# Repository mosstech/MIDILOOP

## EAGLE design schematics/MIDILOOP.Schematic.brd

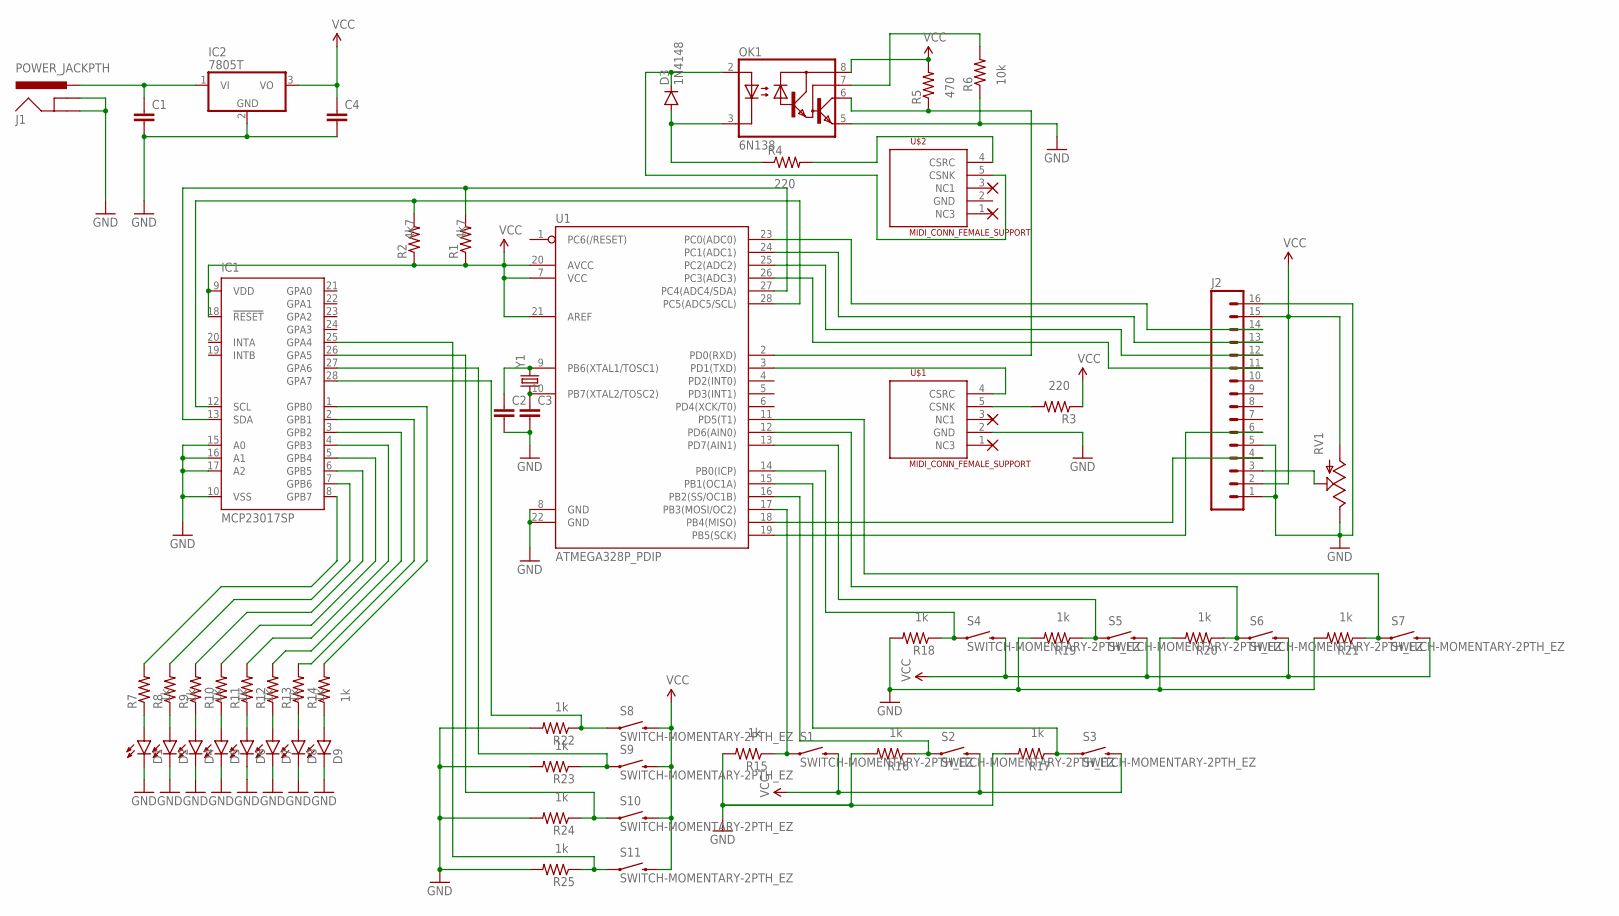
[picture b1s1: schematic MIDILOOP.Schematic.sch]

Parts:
C1, C4: CAPPTH1; CAP-PTH-5MM
C2, C3: CAPPTH; CAP-PTH-SMALL
D1, D2, D4, D5, D6, D7, D8, D9: LED3MM
D3: 1N4148; DIODE-1N4148
IC1: MCP23017SP; DIL28-3
IC2: 7805T; TO220H
J1: POWER_JACKPTH; POWER_JACK_PTH
J2: M16LONGPADS; 1X16_LONGPADS
OK1: 6N138; DIL08
R1, R2, R3, R4, R5, R6, R7, R8, R9, R10, R11, R12, R13, R14, R15, R16, R17, R18, R19, R20, R21, R22, R23, R24, R25: RESISTOREZ; AXIAL-0.3EZ
RV1: POTTRIM; TRIM_POT
S1, S2, S3, S4, S5, S6, S7, S8, S9, S10, S11: SWITCH-MOMENTARY-2PTH_EZ; TACTILE-PTH-EZ
U1: ATMEGA328P_PDIP; DIL28-3
U$1, U$2: MIDI_CONN_FEMALE_SUPPORT; DIN_5_FEMALE_SUPPORT
Y1: CRYSTALHC49US; HC49US

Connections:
GND: C1.2, C2.2, C3.2, C4.2, D1.K (C), D2.K (C), D4.K (C), D5.K (C), D6.K (C), D7.K (C), D8.K (C), D9.K (C), IC1.10 (VSS), IC1.15 (A0), IC1.16 (A1), IC1.17 (A2), IC2.2 (GND), J1.GND, J1.GNDBREAK, J2.1, J2.5, J2.16, OK1.5 (GND), R6.P$1 (1), R15.P$2 (2), R16.P$2 (2), R17.P$2 (2), R18.P$2 (2), R19.P$2 (2), R20.P$2 (2), R21.P$2 (2), R22.P$2 (2), R23.P$2 (2), R24.P$2 (2), R25.P$2 (2), RV1.2 (E), U1.8 (GND), U1.22 (GND), U$1.2 (GND)
unnamed: C2.1, U1.9 (PB6(XTAL1/TOSC1)), Y1.2
unnamed: U1.3 (PD1(TXD)), U$1.4 (CSRC)
unnamed: IC1.13 (SDA), R1.P$2 (2), U1.27 (PC4(ADC4/SDA))
unnamed: IC1.12 (SCL), R2.P$2 (2), U1.28 (PC5(ADC5/SCL))
unnamed: C3.1, U1.10 (PB7(XTAL2/TOSC2)), Y1.1
unnamed: R3.P$2 (2), U$1.5 (CSNK)
unnamed: R4.P$2 (2), U$2.4 (CSRC)
unnamed: D3.C, OK1.2 (A), U$2.5 (CSNK)
unnamed: D3.A, OK1.3 (C), R4.P$1 (1)
unnamed: IC1.8 (GPB7), R7.P$2 (2)
unnamed: OK1.6 (VO), R5.P$1 (1), U1.2 (PD0(RXD))
unnamed: OK1.7 (VB), R6.P$2 (2)
unnamed: D1.A, R7.P$1 (1)
unnamed: IC1.7 (GPB6), R8.P$2 (2)
unnamed: D2.A, R8.P$1 (1)
unnamed: IC1.6 (GPB5), R9.P$2 (2)
unnamed: IC1.4 (GPB3), R11.P$2 (2)
unnamed: IC1.3 (GPB2), R12.P$2 (2)
unnamed: IC1.2 (GPB1), R13.P$2 (2)
unnamed: IC1.1 (GPB0), R14.P$2 (2)
unnamed: D4.A, R9.P$1 (1)
unnamed: D5.A, R10.P$1 (1)
unnamed: D6.A, R11.P$1 (1)
unnamed: D7.A, R12.P$1 (1)
unnamed: D8.A, R13.P$1 (1)
unnamed: D9.A, R14.P$1 (1)
unnamed: R15.P$1 (1), S1.1, U1.17 (PB3(MOSI/OC2))
unnamed: R18.P$1 (1), S4.1, U1.14 (PB0(ICP))
unnamed: R16.P$1 (1), S2.1, U1.16 (PB2(SS/OC1B))
unnamed: R17.P$1 (1), S3.1, U1.15 (PB1(OC1A))
unnamed: R19.P$1 (1), S5.1, U1.13 (PD7(AIN1))
unnamed: J2.3, RV1.1 (S)
unnamed: R20.P$1 (1), S6.1, U1.12 (PD6(AIN0))
unnamed: J2.4, U1.18 (PB4(MISO))
unnamed: J2.6, U1.19 (PB5(SCK))
unnamed: R21.P$1 (1), S7.1, U1.11 (PD5(T1))
unnamed: J2.14, U1.23 (PC0(ADC0))
unnamed: J2.11, U1.26 (PC3(ADC3))
unnamed: J2.12, U1.25 (PC2(ADC2))
unnamed: J2.13, U1.24 (PC1(ADC1))
unnamed: IC1.27 (GPA6), R23.P$1 (1), S9.1
unnamed: IC1.28 (GPA7), R22.P$1 (1), S8.1
unnamed: IC1.26 (GPA5), R24.P$1 (1), S10.1
unnamed: IC1.25 (GPA4), R25.P$1 (1), S11.1
unnamed: C1.1, IC2.1 (VI), J1.PWR
unnamed: IC1.5 (GPB4), R10.P$2 (2)
VCC: C4.1, IC1.9 (VDD), IC1.18 (!RESET), IC2.3 (VO), J2.2, J2.15, OK1.8 (VCC), R1.P$1 (1), R2.P$1 (1), R3.P$1 (1), R5.P$2 (2), RV1.3 (A), S1.3 (2), S2.3 (2), S3.3 (2), S4.3 (2), S5.3 (2), S6.3 (2), S7.3 (2), S8.3 (2), S9.3 (2), S10.3 (2), S11.3 (2), U1.7 (VCC), U1.20 (AVCC), U1.21 (AREF)

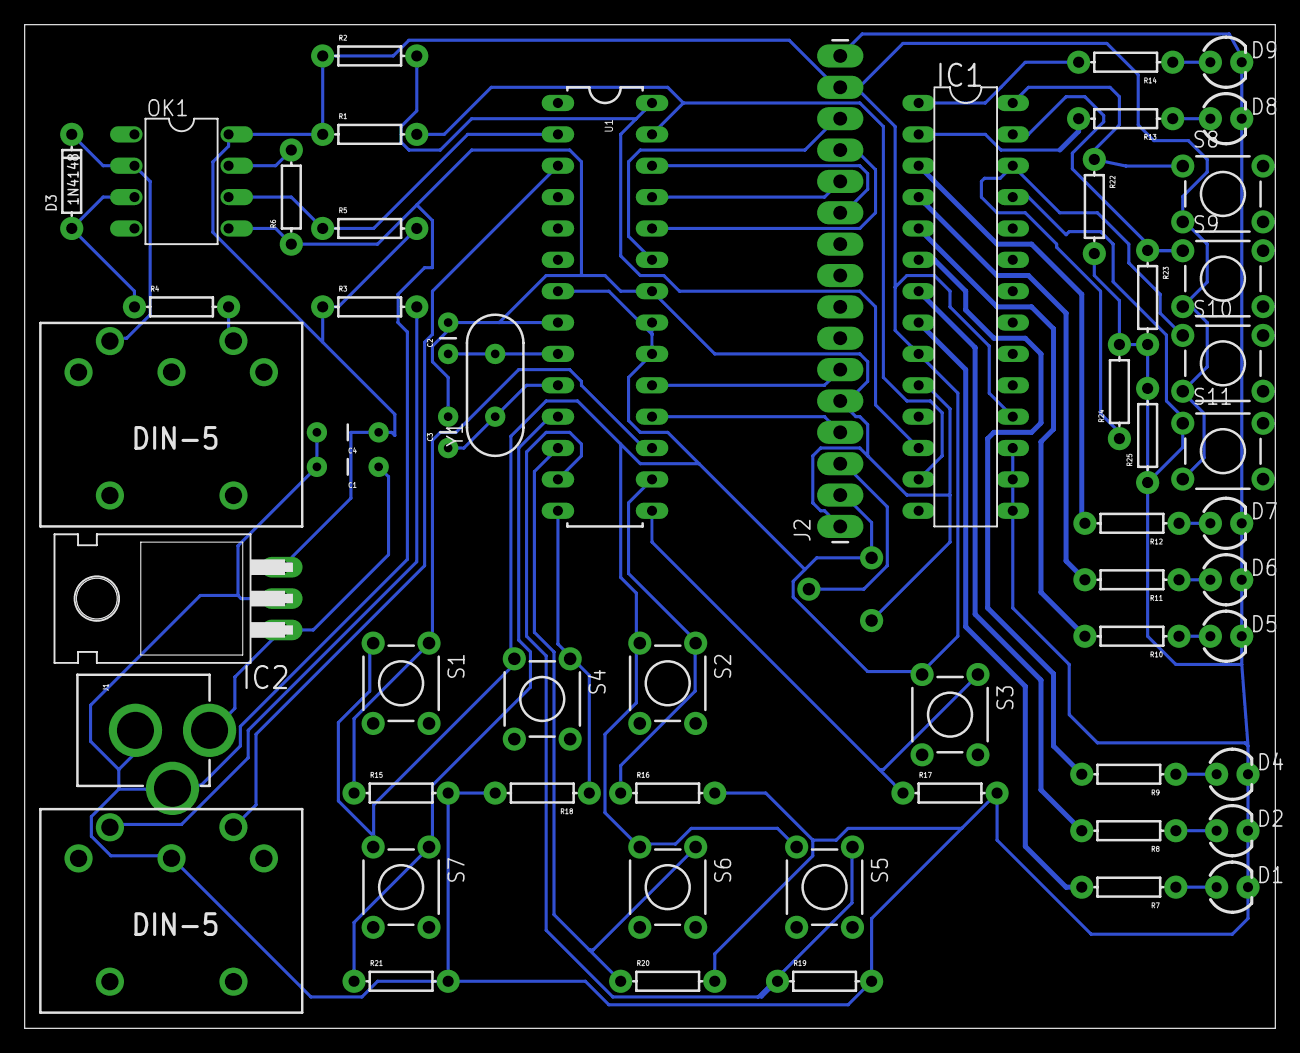
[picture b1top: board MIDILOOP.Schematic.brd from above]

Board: 2 copper layers, 101.3 x 81.3 mm, 59 parts (0 on the bottom side), 48 nets.

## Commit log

2016-02-27 Initial Commit. Pending testing.
2016-03-20 Pin and LED updates
    Updated pin numbers and LED display alignment
2016-03-20 LCD Updates
    Created intToString method to convert an int into a 2-length string.
    Also fixed quantize display justification

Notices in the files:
parts and their libraries:
SparkFun-Passives: Licensing: Creative Commons ShareAlike 4.0 International - https://creativecommons.org/licenses/by-sa/4.0
